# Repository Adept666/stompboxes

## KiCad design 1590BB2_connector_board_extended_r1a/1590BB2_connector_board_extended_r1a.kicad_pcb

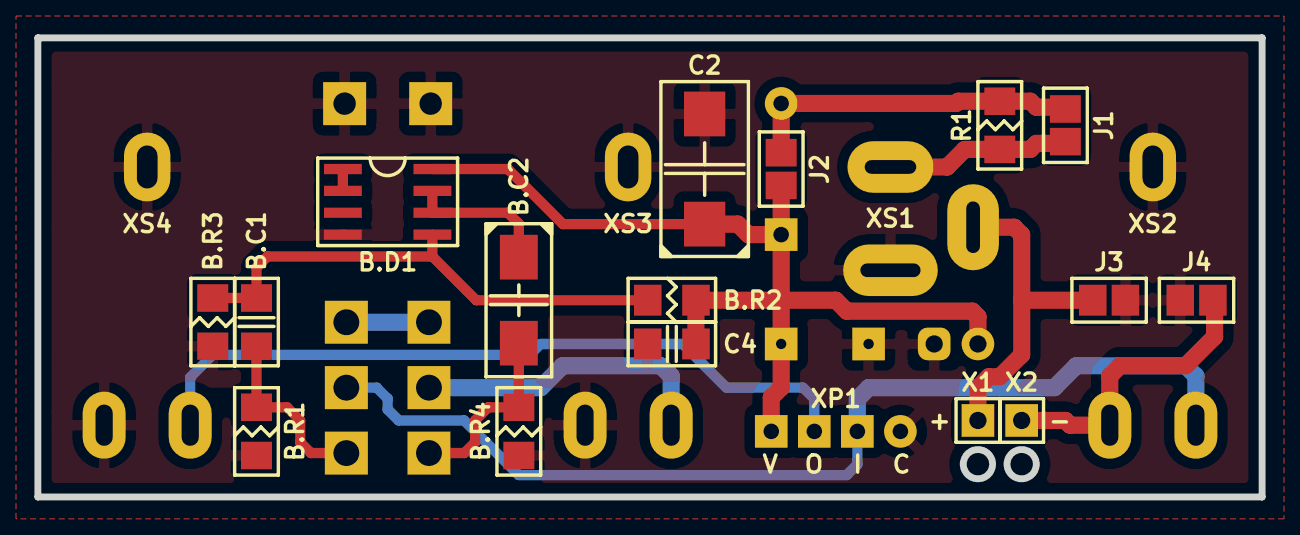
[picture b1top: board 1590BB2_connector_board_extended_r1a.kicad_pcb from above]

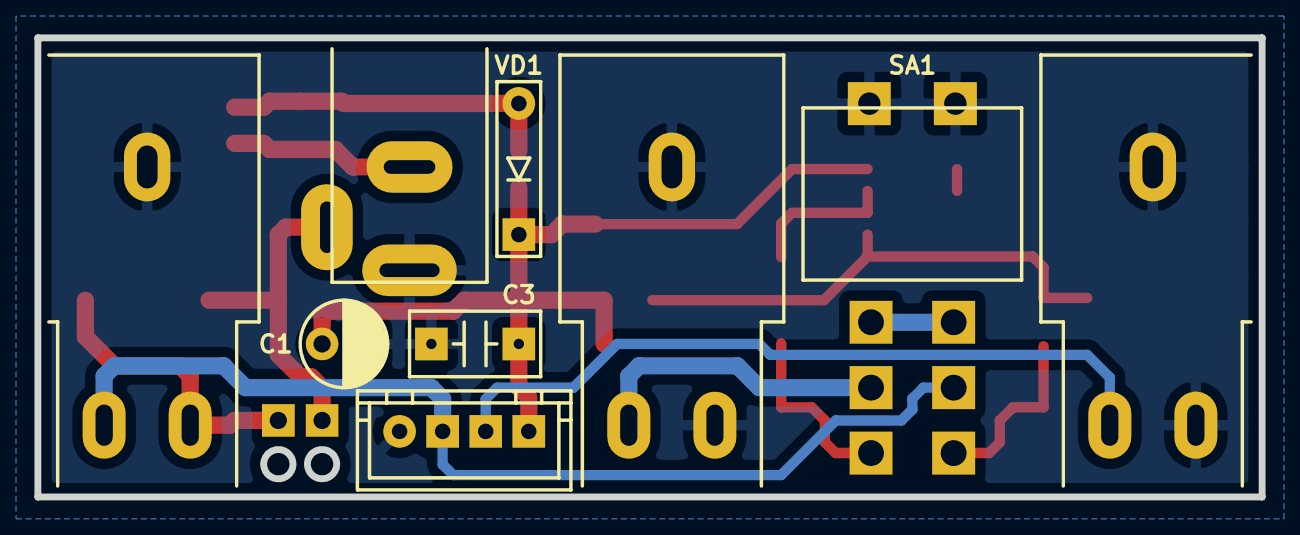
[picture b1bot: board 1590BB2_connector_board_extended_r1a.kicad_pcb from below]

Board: 2 copper layers, 71.1 x 26.7 mm, 26 parts (9 on the bottom side), 15 nets.

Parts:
B.C1: 105; C-SM-1206
B.C2: 106; CP-CTSMD-C
B.D1: 4558; P-SO-08
B.R1, B.R2, B.R3, B.R4: 105; R-SM-1206
C1: 107; CP-RADIAL-D05.0-P02.0-CLS
C2: 107; CP-CTSMD-D
C3: 104; C-DISK-D04.2-T03.0-P05.08-d0.5
C4: 104; C-SM-1206
GB1: PP3; B-PP3-HV
J1: J1; J-SB-1206-2
J2: J2; J-SB-1206-2
J3: J3; J-SB-1206-2
J4: J4; J-SB-1206-2
R1: 470; R-SM-1206
SA1: MTS-202-C4; SW-MTS-202-C4-2.5
VD1: 5817; P-DO-41
X1: +; CON-PAD-S-1.0-1.9
X2: -; CON-PAD-S-1.0-1.9
XP1: B4B-XH-A; CON-XH-B4B-A
XS1: DC-005; CON-DC-005-9V-OVAL
XS2: PJ-651A-01; CON-PJ-651A-01-IN-OVAL
XS3: PJ-651A-01; CON-PJ-651A-01-DRY-OUT-OVAL
XS4: PJ-651A-01; CON-PJ-651A-01-OUT-OVAL

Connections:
/BUF-IN: B.C1.1, B.R1.2, SA1.NC1
/BUF-OUT: B.C2.-, B.R4.2, SA1.NC2
/DRY-OUT-CON: SA1.COM2, XS3.T
/IN-CON: SA1.COM1, XP1.2, XS2.T
/OUT-CON: XP1.3, XS4.T
/PP3-NEG: J4.1, X2.1, XS2.R
/PP3-POS: J3.1, X1.1, XS1.SN
COM: B.D1.4, B.R1.1, B.R3.1, B.R4.1, C1.-, C2.-, C3.2, C4.2, J3.2, J4.2, SA1.0, XP1.1, XS1.C, XS2.S, XS3.R, XS3.S, XS4.R, XS4.S
unnamed: B.C1.2, B.D1.5, B.R2.1, B.R3.2
unnamed: B.C2.+, B.D1.6, B.D1.7
unnamed: B.D1.1, B.D1.2
unnamed: J1.1, R1.1, XS1.S
unnamed: J1.2, J2.1, R1.2, VD1.A
unnamed: SA1.NO1, SA1.NO2
V: B.D1.8, B.R2.2, C1.+, C2.+, C3.1, C4.1, J2.2, VD1.C, XP1.4

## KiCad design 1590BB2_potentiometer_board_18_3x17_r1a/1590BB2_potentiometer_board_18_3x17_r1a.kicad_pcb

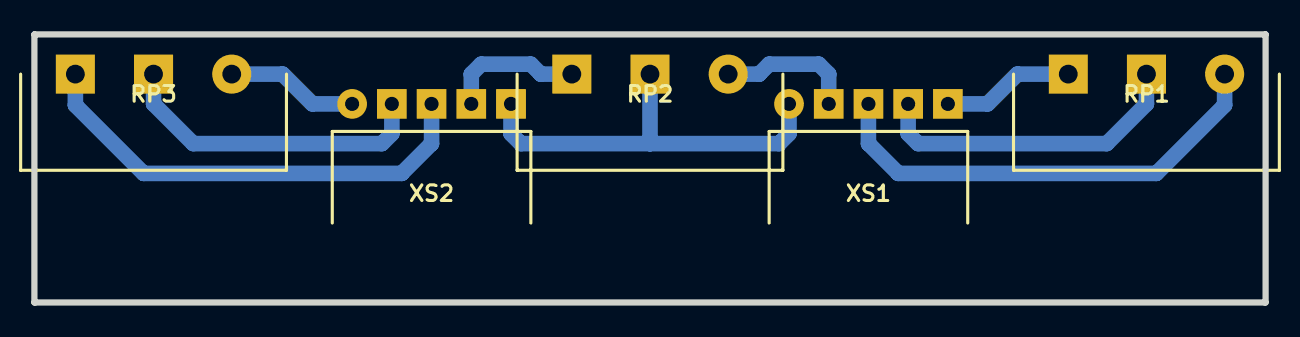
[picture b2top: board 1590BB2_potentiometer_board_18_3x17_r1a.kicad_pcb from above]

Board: 2 copper layers, 78.7 x 17.1 mm, 5 parts (0 on the bottom side), 9 nets.

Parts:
RP1: RP1: 16/17; RP-PDB181-K-20-P
RP2: RP2: 16/17; RP-PDB181-K-20-P
RP3: RP3: 16/17; RP-PDB181-K-20-P
XS1, XS2: PBS-05R; CON-PBS-05R

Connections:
unnamed: RP1.1, XS1.3
unnamed: RP1.2, XS1.4
unnamed: RP1.3, XS1.5
unnamed: RP2.1, XS1.2
unnamed: RP2.2, XS1.1, XS2.5
unnamed: RP2.3, XS2.4
unnamed: RP3.1, XS2.1
unnamed: RP3.2, XS2.2
unnamed: RP3.3, XS2.3

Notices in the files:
1590BB2_connector_board_extended_r1a/1590BB2_connector_board_extended_r1a.kicad_pcb:
This project is licensed under GNU General Public License v3.0 or later
